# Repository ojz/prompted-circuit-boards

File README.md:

---
status: "maintained"
owner: "collaborating agents"
read_when: "arriving at the repository or locating the workflow and documents"
update_when: "entry points, architecture or document locations change; keep live test results in the handoff"
retire_when: "the repository is retired or a replacement entry point is deliberately adopted"
---

# prompted-circuit-boards

Prompt-driven design of a Eurorack instrument, **played in VCV Rack before
it is built in hardware**. Build digital versions of the proposed modules,
try real patches, and learn whether the instrument has a useful balance of
VCAs, LFOs, envelopes, voices and utilities before committing to physical designs.

The existing hardware toolchain is retained: modules are described in Haskell,
KiCad projects are generated from those descriptions, and KiCad's command-line
tools verify them and produce the files JLCPCB needs. The KiCad GUI is a viewer,
not an editor. Hardware work resumes after the musical prototype gate, with
electrical verification, physical measurements and purchase approval still required.

[docs/README.md](docs/README.md) is the document index. Start with
[docs/HANDOFF.md](docs/HANDOFF.md) for the current evidence and next action,
[docs/ROADMAP.md](docs/ROADMAP.md) for priorities and acceptance gates, and
[docs/SETUP.md](docs/SETUP.md) for workstation setup. Standing agent rules are
in [AGENTS.md](AGENTS.md).

For a short explanation of the code, use the
[code map](docs/README.md#where-the-code-lives). These are tools that design and
check hardware on the laptop, plus the panel sketcher. VCV Rack adds playable
desktop prototypes; it does not choose firmware for the eventual modules.

The design direction is to reuse proven circuit approaches and validate them
to explicit precision requirements, not invent new circuitry for novelty.
When a researched decision needs the user's input, the agent creates an editable
question in [docs/decisions/README.md](docs/decisions/README.md)'s inbox workflow.

## Why this shape

The first module (a passive multiple) was built by driving KiCad's editor
through an MCP server. Everything that touched files directly worked; everything
that needed a live editor window was brittle: routing and copper pours only
worked over KiCad's API, zones could not be deleted, footprints could not be
flipped, and footprints created through the API were degraded copies that
failed KiCad's own library check. Half the session went to opening and closing
windows.

The fix is to treat KiCad as a compile target. A design is a small Haskell
value. A generator turns it into `.kicad_sch`, `.kicad_pcb`, `.kicad_pro` and
`.kicad_dru` files that KiCad accepts as its own, and headless tools do the
rest. Nothing depends on a window being open, and regenerating a module is a
one-line command that produces byte-identical files. The MCP server has since
been removed.

## What we use, and why

| Tool | Role | Why |
|------|------|-----|
| **VCV Rack** | Playable digital versions of candidate modules and representative instrument patches. | Learn the musical behavior and simultaneous demand for VCAs, LFOs and other functions before hardware design; a virtual patch is not electrical or safety evidence. |
| **KiCad 10** | Symbol and footprint libraries, ERC/DRC, zone filling, exports and renders. | Headless native checks provide independent design-consistency evidence. Library agreement is not manufacturer-datasheet verification. |
| **pcbgen** (`toolkit/`, Haskell) | Turns a design description into a complete KiCad project. | Structured circuit definitions, design validation and deterministic identifiers make changes reviewable. Types, tests and native checks address different failure modes; none alone proves electrical correctness. |
| **pcbgen router** (`toolkit/src/Route/`) | Routes the declared nets on a two-layer grid, with negotiated congestion and any-angle simplification. | Generates per-design reports under `docs/modules/`. Native KiCad checks remain a separate gate; the benchmark's selected geometry checks are not full DRC. |
| **kicad-cli** | ERC, DRC with schematic parity, zone refill, SVG/PNG renders, fabrication exports. | Exit codes gate commits. The repo rule is that no schematic or layout change lands without a clean ERC and DRC. |
| **KiKit** | JLCPCB fabrication bundle (Gerbers, drill, BOM, CPL) and panelization of several modules into one order. | Headless, scriptable, supports KiCad 10 since v1.8.0, and replaces the GUI-only Fabrication Toolkit plugin. Runs on KiCad's bundled Python. |
| **kicad-happy** skills | Design review, EMC and DFM checks, distributor lookups. | Independent second opinion on a generated design before ordering. |
| **ngspice and NumPy** | Circuit experiments and supporting field calculations. | Numerical evidence with explicit model limits; not a substitute for physical measurement. |
| **Freerouting** | External comparison baseline for the routing benchmark. | Compared through KiCad's DSN/SES interface; not the generator's production routing path. |

## Workflow

1. Build playable digital versions of the candidate modules in VCV Rack,
   recording the intended behavior, any approximations and plugin dependencies.
2. Play representative patches and count the functions needed at the same time.
   Revise module behavior, grouping and quantities from the user's experience.
3. Agree the musical composition before resuming hardware design. The
   [V0 gate](docs/ROADMAP.md#v0-playable-digital-modules-and-function-balance-current)
   owns acceptance; [setup](docs/SETUP.md#vcv-rack) owns the prototype environment.

### Hardware Workflow (Deferred)

This existing pipeline remains available for the hardware stage; it does not
generate or verify the VCV Rack prototypes.

1. Describe or change a module in `modules/<name>/<Name>.hs` and write or
   update `docs/modules/<name>/SPEC.md` with the operating limits, geometry and
   intent. Today the Haskell design supplies the netlist and placement. The
   [module sketcher](docs/SKETCHER.md) can lay out a module idea on a grid
   first, but the bridge from a sketch into a design is not implemented, so a
   sketch is not yet an input to generation.
2. Generate the KiCad projects from the repository root (`all`, or one design
   name):
   ```
   cabal run pcbgen -- all
   ```
   Files land in `modules/<name>/kicad/` (and `modules/<name>/kicad/panel/`
   for an existing front panel), with reports in `docs/modules/<name>/route-report.md`.
   Generated files are never edited by hand; they are committed so the repo
   shows the result. `--out DIR` keeps a custom bundle's report in `DIR/docs/`.
3. Verify headlessly. This copies the project to `modules/<name>/build/`, runs
   ERC, DRC with zone refill and schematic parity, and renders both sides:
   ```
   toolkit/check.sh mult
   toolkit/check.sh mult panel
   ```
4. Look at the renders in `build/`, or open the project in KiCad to inspect it.
5. Run circuit experiments separately with `toolkit/sim.sh <name>` where
   decks exist. The source netlist is generated from the same Haskell design.
6. After checks and the documented design review, export a diagnostic JLCPCB
   bundle with KiKit. Output goes to `build/fab/` and is never committed:
   ```
   toolkit/fab.sh mult
   ```

`toolkit/pipeline.sh <name> [--fab]` combines generation, native checks and
optional export. Final panel artwork and fabrication remain deferred; the
[shared panel language](docs/MECHANICAL.md#panel-layout-language) is adopted
and the [module sketcher](docs/SKETCHER.md) is built, a local HTML editor
that puts components on a grid and produces no circuit and no cutting file. An export does not
constitute approval to purchase or a claim of measured performance.

## Repository layout

```
pcbgen.cabal        the Haskell package; cabal runs from the repo root
toolkit/src/        pcbgen: design model, KiCad emitters, router
toolkit/app/        pcbgen executable and design registry
toolkit/*.sh        generation/check/export orchestration and regression checks
lib/footprints/     footprints the official KiCad library lacks
modules/<name>/     one directory per module:
  <Name>.hs           design source (module), <Name>Panel.hs (front panel)
  kicad/, kicad/panel/  generated KiCad projects (committed)
  build/              verification and fabrication output (ignored)
sketcher/          the browser grid editor; catalogue.js and vectors.js are generated
sketches/          saved module sketches; _fixtures/ is generated
docs/              specifications, setup, roadmap, handoff and generated reports
   decisions/         editable user decision inbox; processed files are retired
   modules/<name>/    specification and generated routing report
AGENTS.md          standing rules, including documentation lifecycle
CLAUDE.md          imports AGENTS.md
```

## Modules

These are retained hardware designs and requirements, not implemented VCV Rack
modules. The broader candidate composition and current prototype work belong
in the roadmap and handoff.

| Module | HP | Scope |
|--------|----|--------|
| [docs/modules/io-mixer/SPEC.md](docs/modules/io-mixer/SPEC.md) | Not fixed | R1: four-channel mono/DC mixer, 3.5 mm stereo consumer audio and USB-C PD power; requirements, not an implemented circuit yet. |
| [docs/modules/mult/SPEC.md](docs/modules/mult/SPEC.md) | 6 | 2x6 passive multiple; no power. |
| [docs/modules/attenuverter/SPEC.md](docs/modules/attenuverter/SPEC.md) | 6 | Dual buffered attenuverter with reference offset normalling. |

Current check results and hardware status belong in
[docs/HANDOFF.md](docs/HANDOFF.md), not a second status table here.

## Eurorack conventions baked in

Mechanical and power conventions are owned by [AGENTS.md](AGENTS.md) and
implemented in [Design.hs](toolkit/src/Design.hs#L1). Each module's specification
records its exact coordinates and exceptions. Manufacturing and physical-fit
evidence must support those conventions before an order; a passing CAD check
does not establish that real parts have been test-fitted.

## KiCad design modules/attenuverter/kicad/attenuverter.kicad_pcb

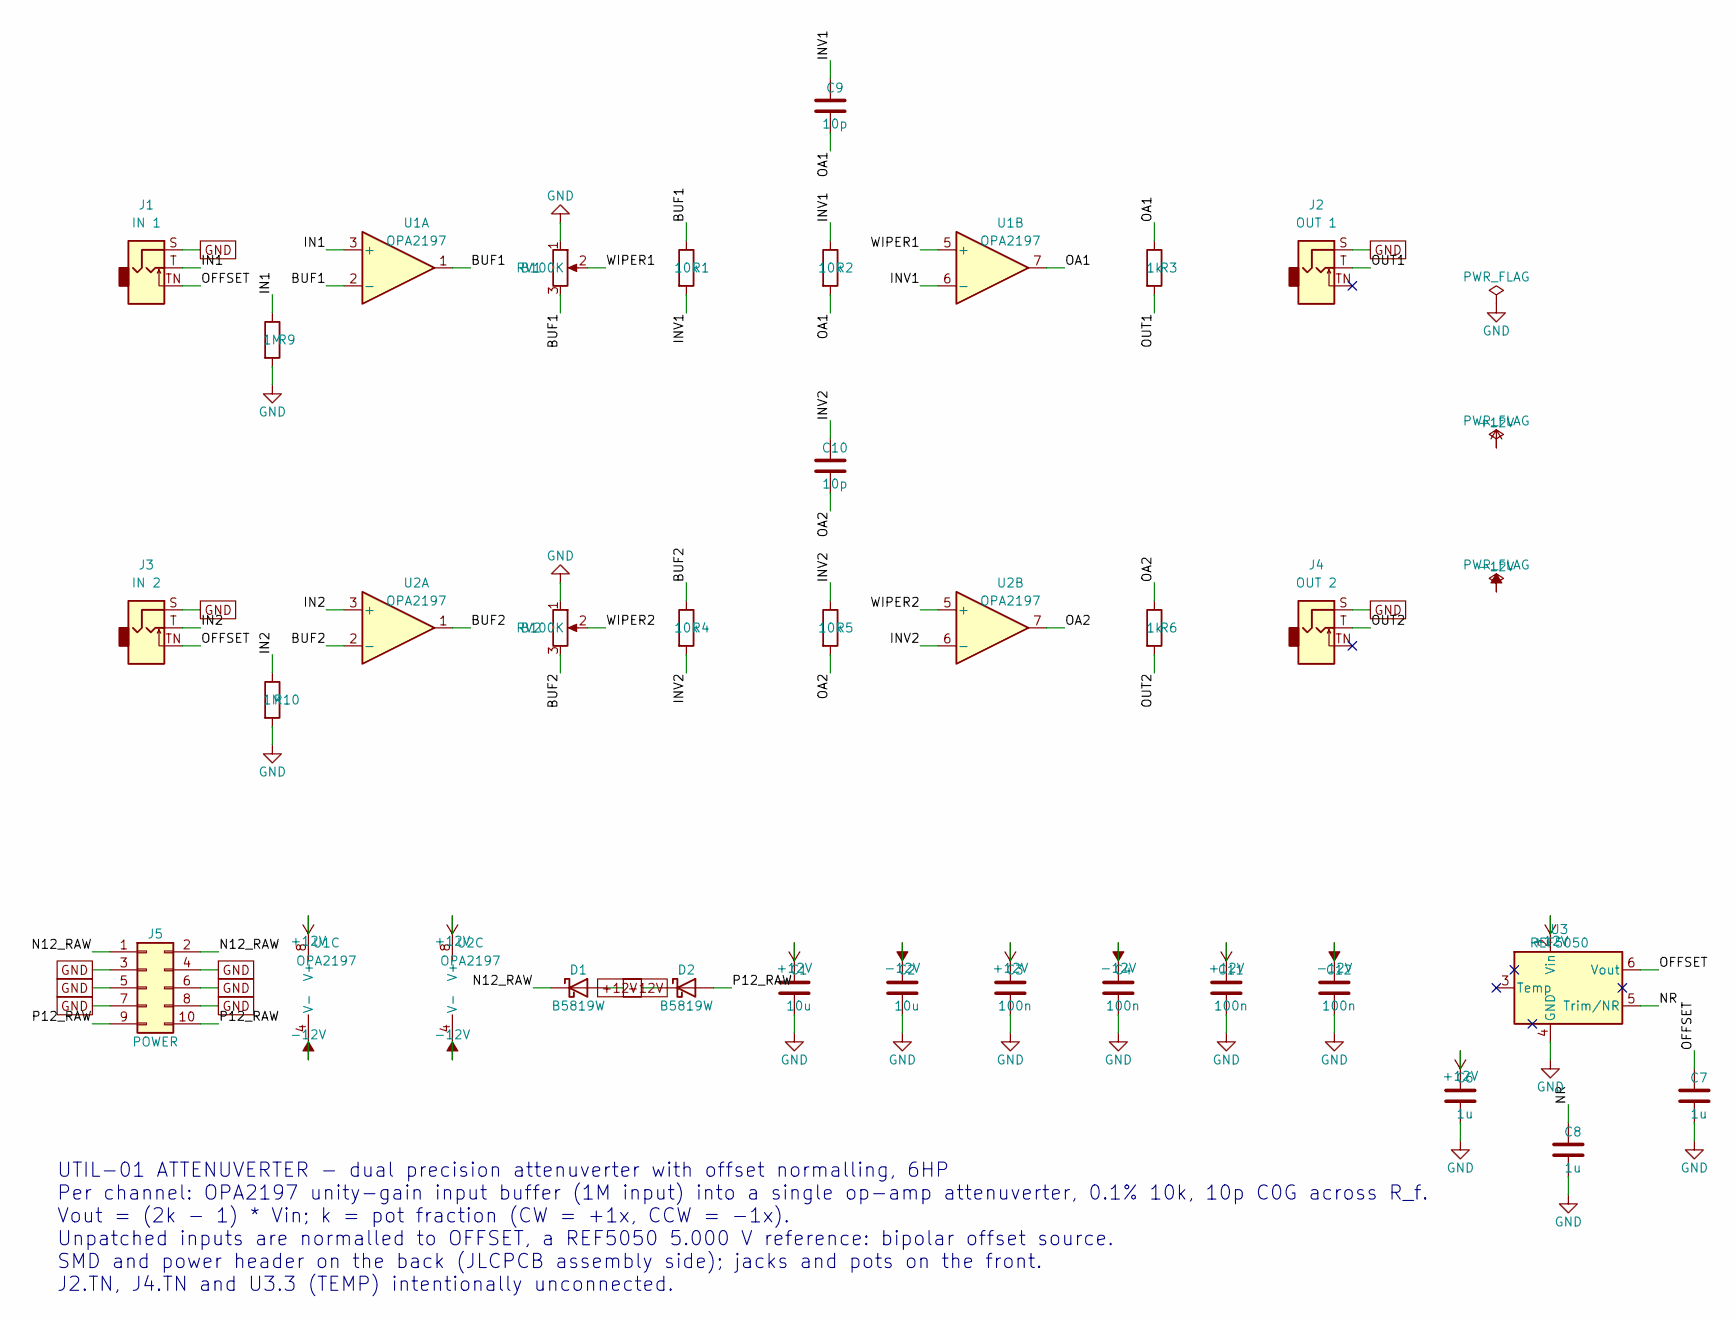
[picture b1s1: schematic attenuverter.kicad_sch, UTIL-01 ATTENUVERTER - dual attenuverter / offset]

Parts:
C1, C2: 10u; C_0805_2012Metric; LCSC Part # C15850
C3, C4, C11, C12: 100n; C_0805_2012Metric; LCSC Part # C49678
C6, C7, C8: 1u; C_0805_2012Metric; LCSC Part # C28323
C9, C10: 10p; C_0805_2012Metric; LCSC Part # C344177
D1, D2: B5819W; D_SOD-123; LCSC Part # C8598
J1: IN 1; Jack_3.5mm_QingPu_WQP-PJ398SM_Vertical_CircularHoles
J2: OUT 1; Jack_3.5mm_QingPu_WQP-PJ398SM_Vertical_CircularHoles
J3: IN 2; Jack_3.5mm_QingPu_WQP-PJ398SM_Vertical_CircularHoles
J4: OUT 2; Jack_3.5mm_QingPu_WQP-PJ398SM_Vertical_CircularHoles
J5: POWER; IDC-Header_2x05_P2.54mm_Vertical
R1, R2, R4, R5: 10k; R_0805_2012Metric; LCSC Part # C110775
R3, R6: 1k; R_0805_2012Metric; LCSC Part # C17513
R9, R10: 1M; R_0805_2012Metric; LCSC Part # C17514
RV1, RV2: B100K; Potentiometer_Alpha_RD901F-40-00D_Single_Vertical
U1, U2: OPA2197; SOIC-8_3.9x4.9mm_P1.27mm; LCSC Part # C139363
U3: REF5050; SOIC-8_3.9x4.9mm_P1.27mm; LCSC Part # C27804

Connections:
+12V: C1.1, C3.1, C6.1, C11.1, D2.1 (K), U1.8 (V+), U2.8 (V+), U3.2 (Vin)
-12V: C2.1, C4.1, C12.1, D1.2 (A), U1.4 (V-), U2.4 (V-)
/BUF1: R1.1, RV1.3, U1.1, U1.2 (-)
/BUF2: R4.1, RV2.3, U2.1, U2.2 (-)
/IN1: J1.T, R9.1, U1.3 (+)
/IN2: J3.T, R10.1, U2.3 (+)
/INV1: C9.1, R1.2, R2.1, U1.6 (-)
/INV2: C10.1, R4.2, R5.1, U2.6 (-)
/N12_RAW: D1.1 (K), J5.1, J5.2
/NR: C8.1, U3.5 (Trim/NR)
/OA1: C9.2, R2.2, R3.1, U1.7
/OA2: C10.2, R5.2, R6.1, U2.7
/OFFSET: C7.1, J1.TN, J3.TN, U3.6 (Vout)
/OUT1: J2.T, R3.2
/OUT2: J4.T, R6.2
/P12_RAW: D2.2 (A), J5.9, J5.10
/WIPER1: RV1.2, U1.5 (+)
/WIPER2: RV2.2, U2.5 (+)
GND: C1.2, C2.2, C3.2, C4.2, C6.2, C7.2, C8.2, C11.2, C12.2, J1.S, J2.S, J3.S, J4.S, J5.3, J5.4, J5.5, J5.6, J5.7, J5.8, R9.2, R10.2, RV1.1, RV2.1, U3.4 (GND)

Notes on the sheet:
UTIL-01 ATTENUVERTER - dual precision attenuverter with offset normalling, 6HP Per channel: OPA2197 unity-gain input buffer (1M input) into a single op-amp attenuverter, 0.1% 10k, 10p C0G across R_f. Vout = (2k - 1) * Vin; k = pot fraction (CW = +1x, CCW = -1x). Unpatched inputs are normalled to OF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

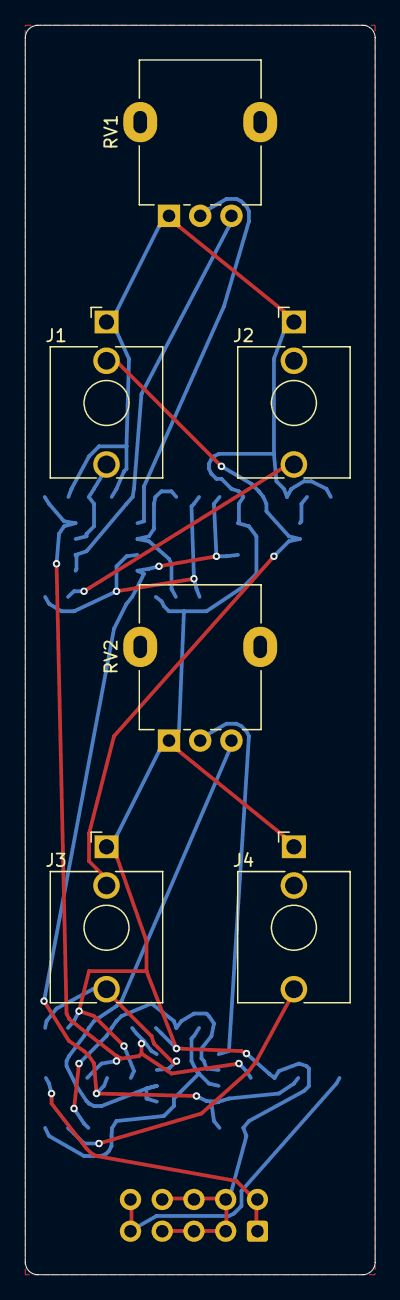
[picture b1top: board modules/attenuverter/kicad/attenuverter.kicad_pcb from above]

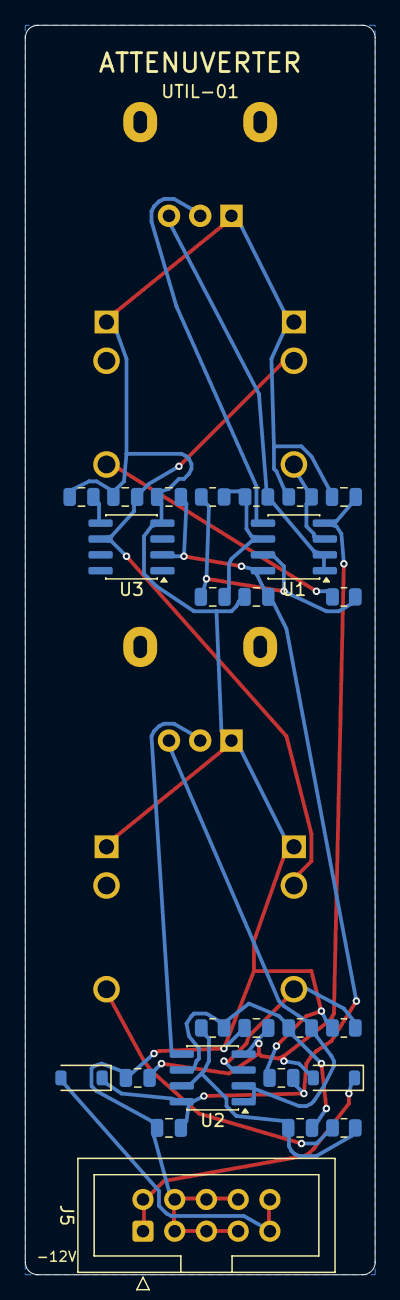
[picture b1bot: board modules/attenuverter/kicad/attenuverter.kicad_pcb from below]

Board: 2 copper layers, 28.0 x 100.0 mm, 31 parts (25 on the bottom side), 19 nets.

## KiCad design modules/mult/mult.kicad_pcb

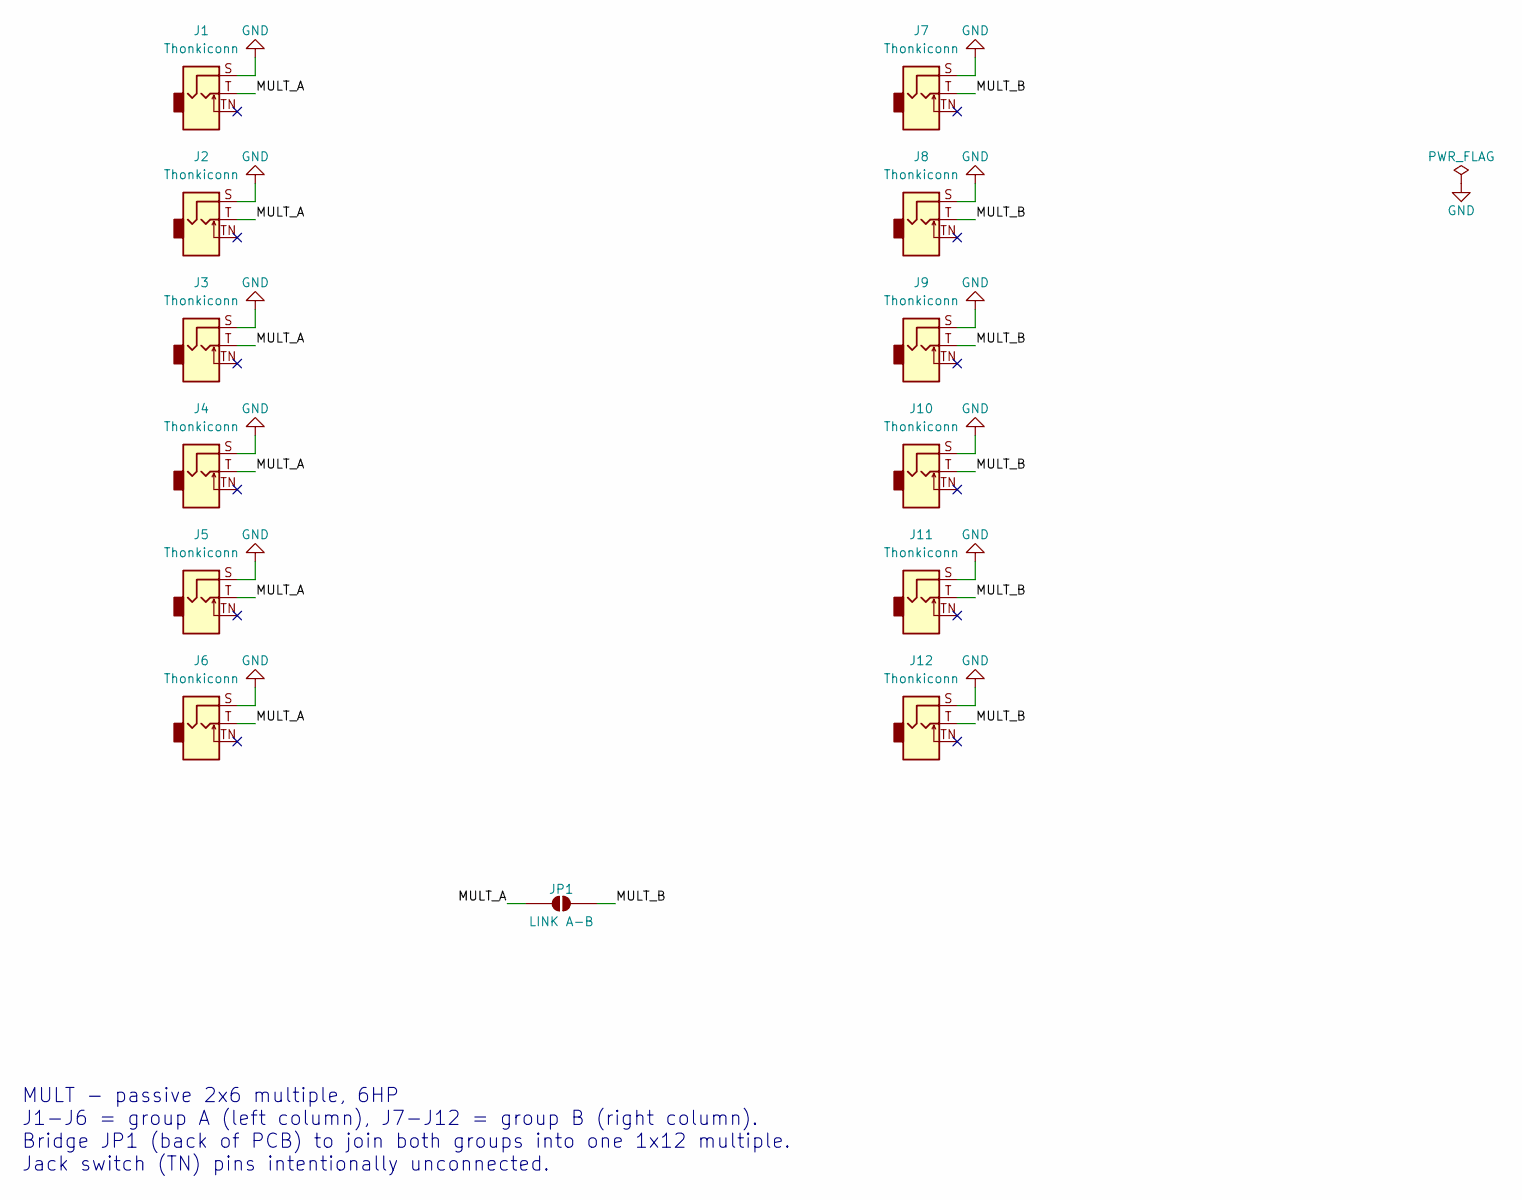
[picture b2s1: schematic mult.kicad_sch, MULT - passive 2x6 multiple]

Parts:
J1, J2, J3, J4, J5, J6, J7, J8, J9, J10, J11, J12: Thonkiconn; Jack_3.5mm_QingPu_WQP-PJ398SM_Vertical_CircularHoles
JP1: LINK A-B; SolderJumper-2_P1.3mm_Open_Pad1.0x1.5mm

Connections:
/MULT_A: J1.T, J2.T, J3.T, J4.T, J5.T, J6.T, JP1.1 (A)
/MULT_B: J7.T, J8.T, J9.T, J10.T, J11.T, J12.T, JP1.2 (B)
GND: J1.S, J2.S, J3.S, J4.S, J5.S, J6.S, J7.S, J8.S, J9.S, J10.S, J11.S, J12.S

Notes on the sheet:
MULT - passive 2x6 multiple, 6HP J1-J6 = group A (left column), J7-J12 = group B (right column). Bridge JP1 (back of PCB) to join both groups into one 1x12 multiple. Jack switch (TN) pins intentionally unconnected.

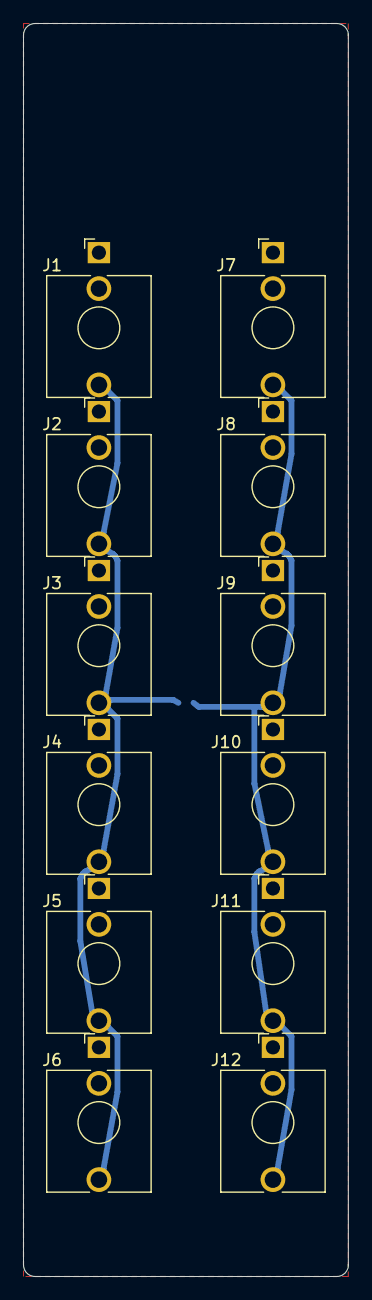
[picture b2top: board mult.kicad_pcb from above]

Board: 2 copper layers, 28.0 x 108.0 mm, 13 parts (1 on the bottom side), 3 nets.

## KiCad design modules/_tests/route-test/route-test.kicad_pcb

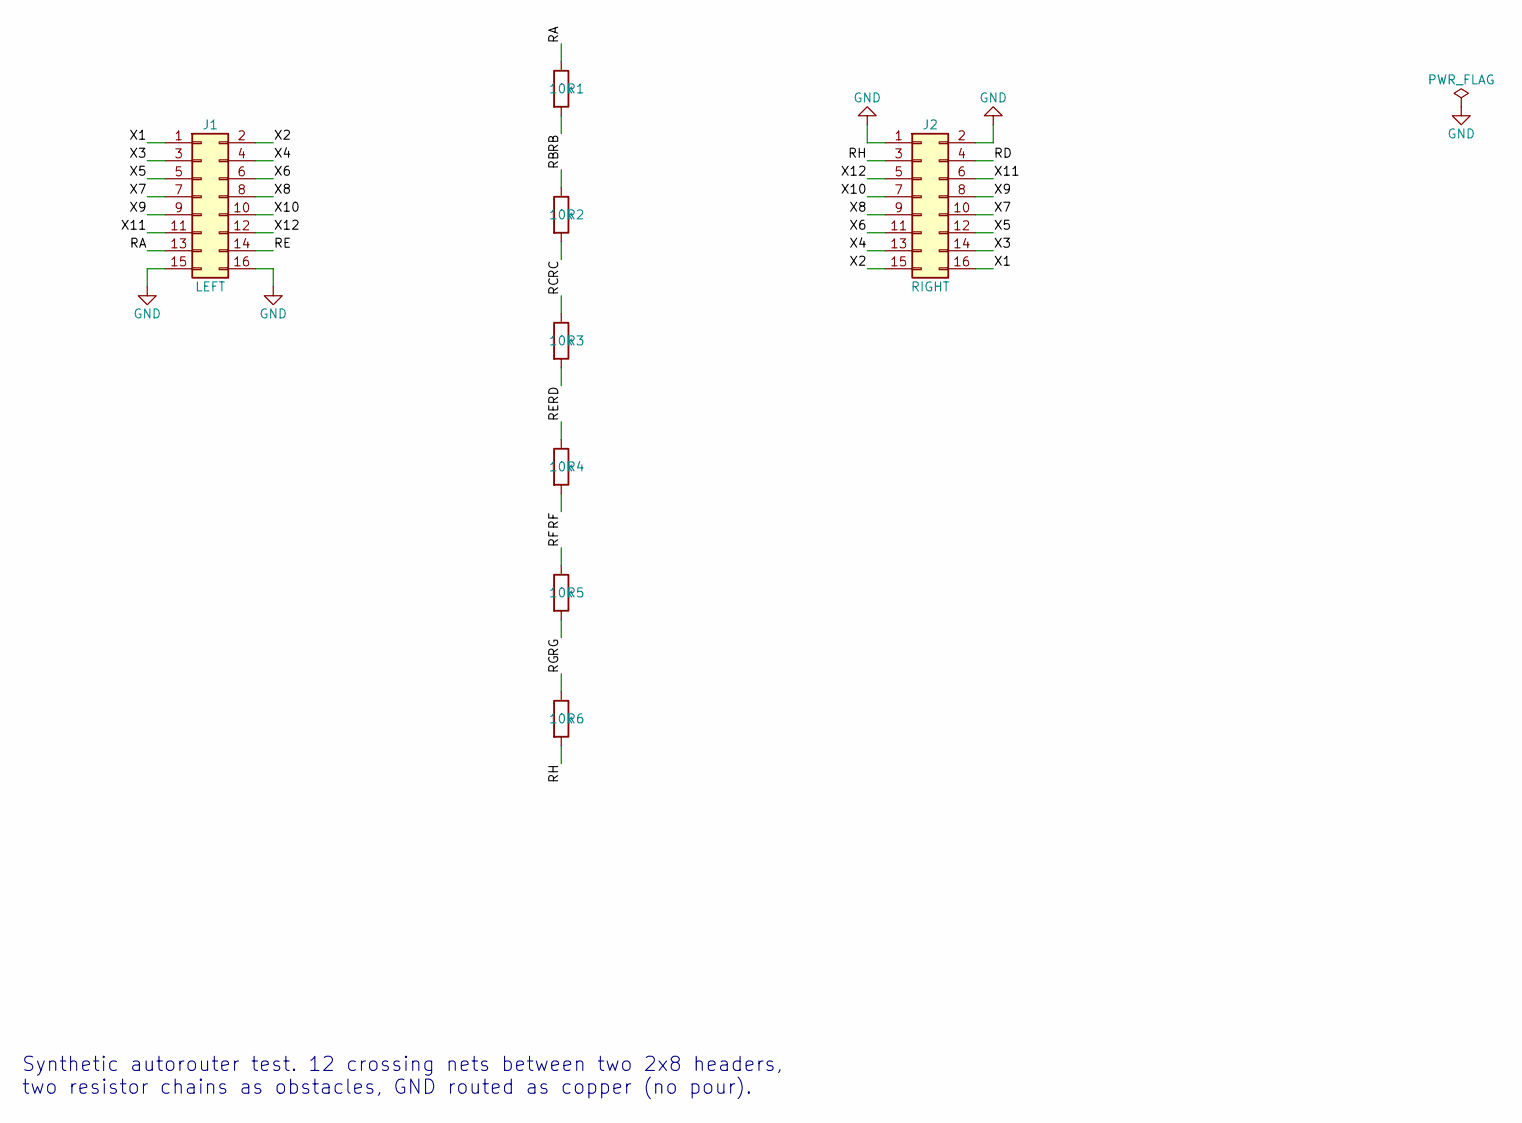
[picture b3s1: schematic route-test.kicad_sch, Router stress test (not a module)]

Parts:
J1: LEFT; PinHeader_2x08_P2.54mm_Vertical
J2: RIGHT; PinHeader_2x08_P2.54mm_Vertical
R1, R2, R3, R4, R5, R6: 10k; R_0805_2012Metric

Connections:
/RA: J1.13, R1.1
/RB: R1.2, R2.1
/RC: R2.2, R3.1
/RD: J2.4, R3.2
/RE: J1.14, R4.1
/RF: R4.2, R5.1
/RG: R5.2, R6.1
/RH: J2.3, R6.2
/X1: J1.1, J2.16
/X2: J1.2, J2.15
/X3: J1.3, J2.14
/X4: J1.4, J2.13
/X5: J1.5, J2.12
/X6: J1.6, J2.11
/X7: J1.7, J2.10
/X8: J1.8, J2.9
/X9: J1.9, J2.8
/X10: J1.10, J2.7
/X11: J1.11, J2.6
/X12: J1.12, J2.5
GND: J1.15, J1.16, J2.1, J2.2

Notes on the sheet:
Synthetic autorouter test. 12 crossing nets between two 2x8 headers, two resistor chains as obstacles, GND routed as copper (no pour).

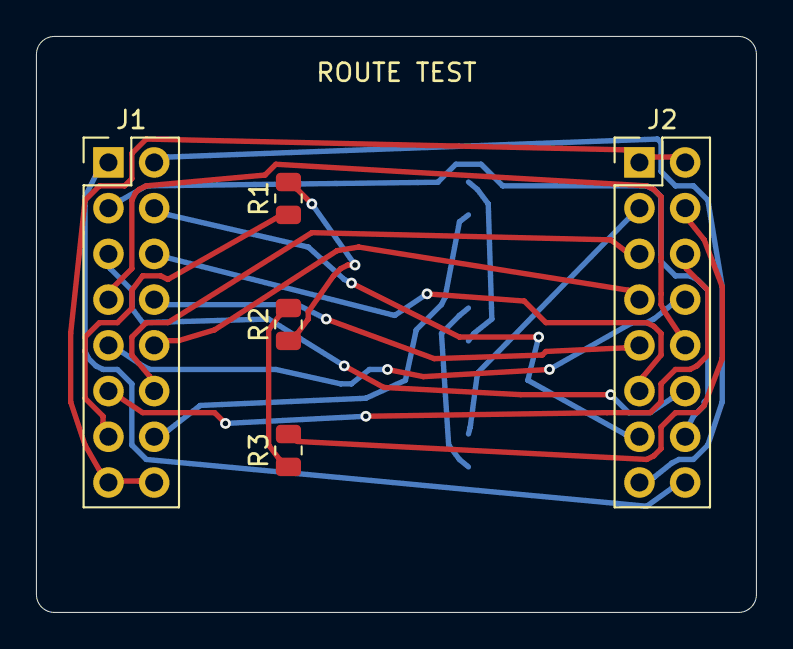
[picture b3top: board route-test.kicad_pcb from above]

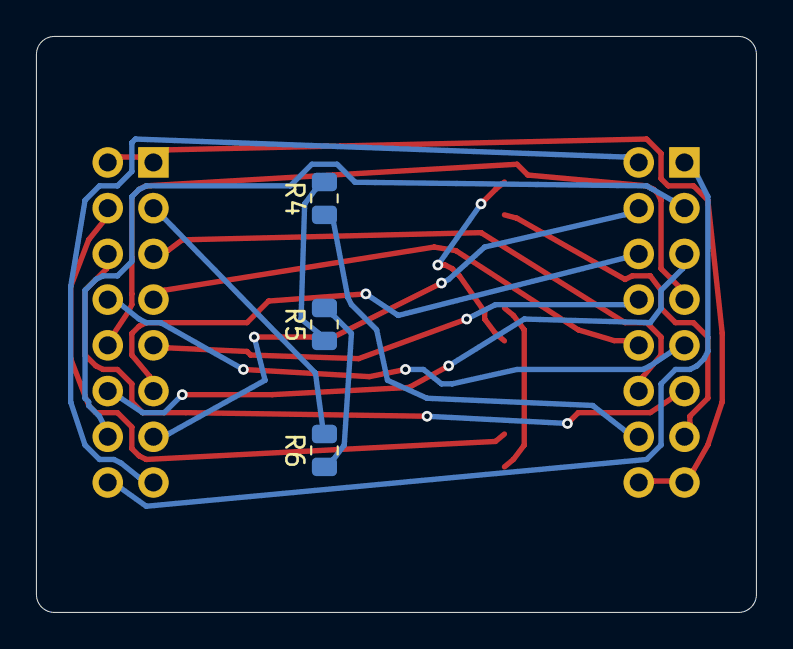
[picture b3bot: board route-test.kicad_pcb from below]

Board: 2 copper layers, 40.0 x 32.0 mm, 8 parts (3 on the bottom side), 21 nets.

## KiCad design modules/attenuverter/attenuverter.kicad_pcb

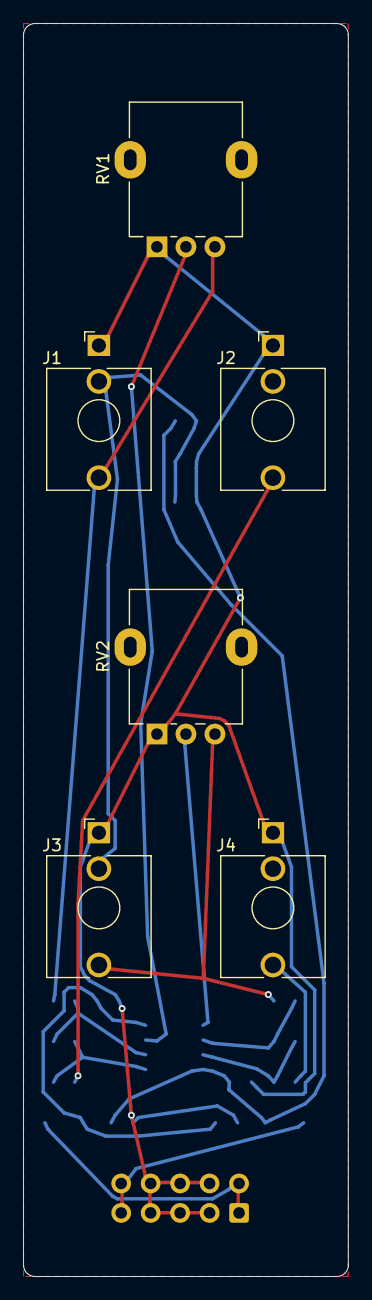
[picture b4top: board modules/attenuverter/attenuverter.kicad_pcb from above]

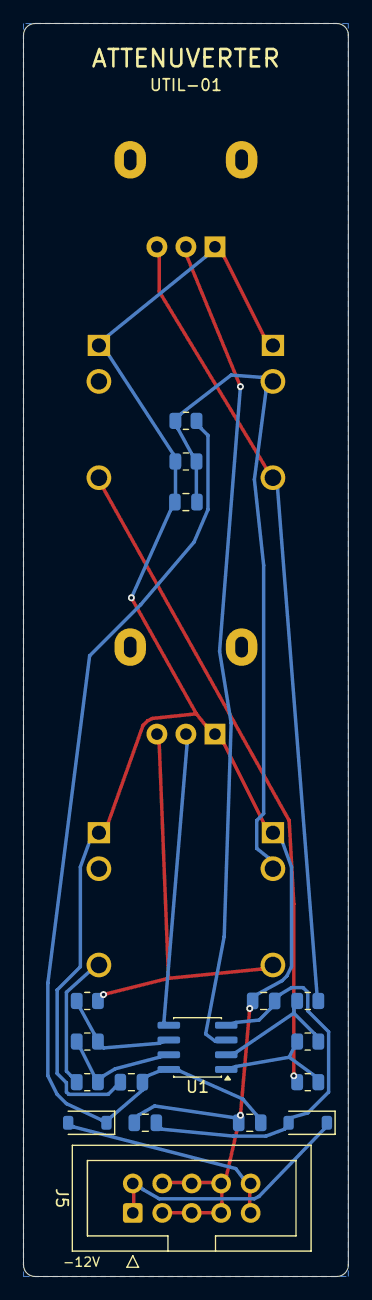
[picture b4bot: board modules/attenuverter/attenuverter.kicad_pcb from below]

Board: 2 copper layers, 28.0 x 108.0 mm, 23 parts (17 on the bottom side), 16 nets.

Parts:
C1, C2: 10u; C_0805_2012Metric
C3, C4, C5: 100n; C_0805_2012Metric
D1, D2: B5819W; D_SOD-123
J1: IN 1; Jack_3.5mm_QingPu_WQP-PJ398SM_Vertical_CircularHoles
J2: OUT 1; Jack_3.5mm_QingPu_WQP-PJ398SM_Vertical_CircularHoles
J3: IN 2; Jack_3.5mm_QingPu_WQP-PJ398SM_Vertical_CircularHoles
J4: OUT 2; Jack_3.5mm_QingPu_WQP-PJ398SM_Vertical_CircularHoles
J5: POWER; IDC-Header_2x05_P2.54mm_Vertical
R1, R2, R4, R5: 100k; R_0805_2012Metric
R3, R6, R8: 1k; R_0805_2012Metric
R7: 1.5k; R_0805_2012Metric
RV1, RV2: B100K; Potentiometer_Alpha_RD901F-40-00D_Single_Vertical
U1: TL072; SOIC-8_3.9x4.9mm_P1.27mm

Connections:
+12V: C1.1, C3.1, D2.1, R7.1, U1.8
-12V: C2.1, C4.1, D1.2, U1.4
/IN1: J1.T, R1.1, RV1.3
/IN2: J3.T, R4.1, RV2.3
/INV1: R1.2, R2.1, U1.2
/INV2: R4.2, R5.1, U1.6
/N12_RAW: D1.1, J5.1, J5.2
/OA1: R2.2, R3.1, U1.1
/OA2: R5.2, R6.1, U1.7
/OFFSET: C5.1, J1.TN, J3.TN, R7.2, R8.1
/OUT1: J2.T, R3.2
/OUT2: J4.T, R6.2
/P12_RAW: D2.2, J5.9, J5.10
/WIPER1: RV1.2, U1.3
/WIPER2: RV2.2, U1.5
GND: C1.2, C2.2, C3.2, C4.2, C5.2, J1.S, J2.S, J3.S, J4.S, J5.3, J5.4, J5.5, J5.6, J5.7, J5.8, R8.2, RV1.1, RV2.1
